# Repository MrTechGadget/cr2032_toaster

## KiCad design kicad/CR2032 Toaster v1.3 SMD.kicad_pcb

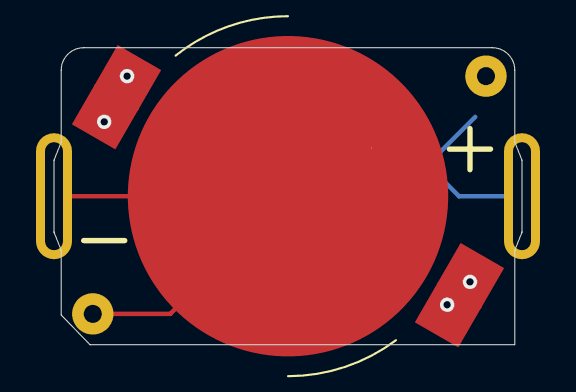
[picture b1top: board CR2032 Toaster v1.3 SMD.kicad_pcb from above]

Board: 2 copper layers, 26.0 x 16.5 mm, 3 parts (0 on the bottom side), 2 nets.

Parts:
BT1: BLK-912; BAT_BAT-HLD-001-THM
J1, J2: Conn_01x01; 6mm PTS

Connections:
unnamed: BT1.N, J2.1
unnamed: BT1.P1, BT1.P2, BT1.P3, BT1.P4, J1.1

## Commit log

2023-04-01 Add spec sheet for BK-912 SMD component
2023-04-01 Duplicate 1.3 kicad files with SMD name
2023-04-01 Changed footprint to SMD and adjusted pad sizes
2023-04-01 Modified 1.3 for SMD, with Gerber File
